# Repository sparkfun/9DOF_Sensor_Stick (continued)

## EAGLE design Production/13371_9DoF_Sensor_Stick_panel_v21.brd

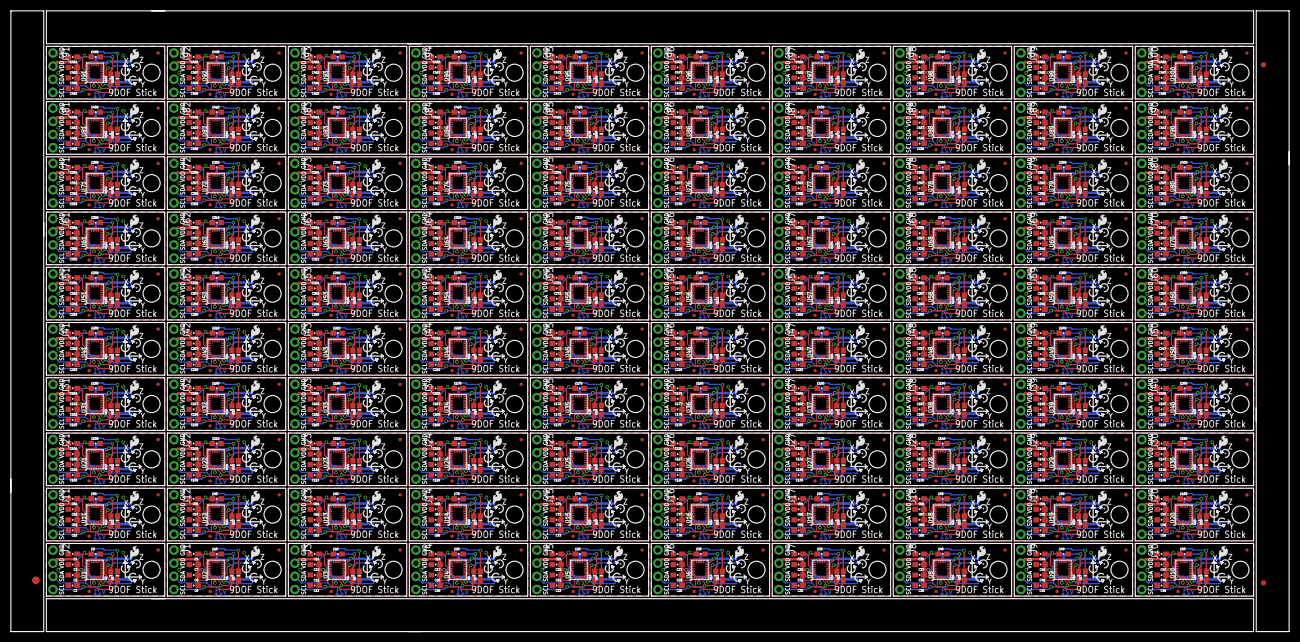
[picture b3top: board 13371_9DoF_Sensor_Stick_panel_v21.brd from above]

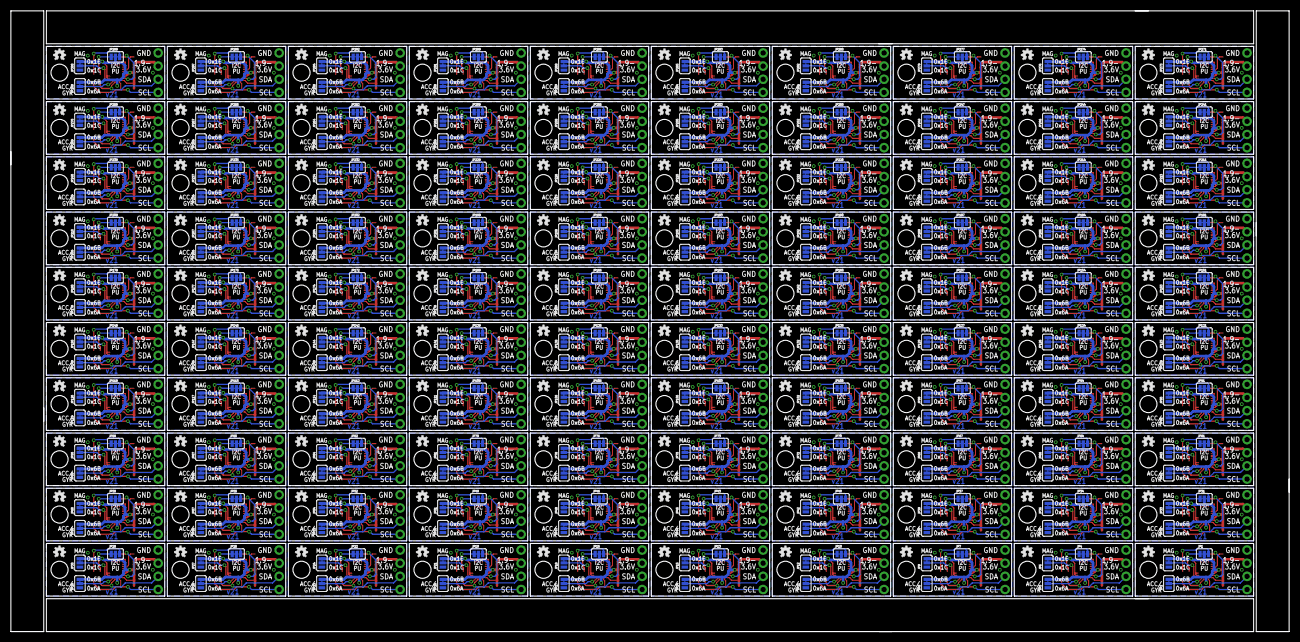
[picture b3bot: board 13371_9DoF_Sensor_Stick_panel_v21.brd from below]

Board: 2 copper layers, 246.9 x 119.9 mm, 1703 parts (400 on the bottom side), 1000 nets.

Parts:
C1, C6, C11, C16, C21, C26, C31, C36, C41, C46, C51, C56, C61, C66, C71, C76, C81, C86, C91, C96, C101, C106, C111, C116, C121, C126, C131, C136, C141, C146, C151, C156, C161, C166, C171, C176, C181, C186, C191, C196, C201, C206, C211, C216, C221, C226, C231, C236, C241, C246, C251, C256, C261, C266, C271, C276, C281, C286, C291, C296, C301, C306, C311, C316, C321, C326, C331, C336, C341, C346, C351, C356, C361, C366, C371, C376, C381, C386, C391, C396, C401, C406, C411, C416, C421, C426, C431, C436, C441, C446, C451, C456, C461, C466, C471, C476, C481, C486, C491, C496: 10uF; 0603-CAP
C2, C3, C5, C7, C8, C10, C12, C13, C15, C17, C18, C20, C22, C23, C25, C27, C28, C30, C32, C33, C35, C37, C38, C40, C42, C43, C45, C47, C48, C50, C52, C53, C55, C57, C58, C60, C62, C63, C65, C67, C68, C70, C72, C73, C75, C77, C78, C80, C82, C83, C85, C87, C88, C90, C92, C93, C95, C97, C98, C100, C102, C103, C105, C107, C108, C110, C112, C113, C115, C117, C118, C120, C122, C123, C125, C127, C128, C130, C132, C133, C135, C137, C138, C140, C142, C143, C145, C147, C148, C150, C152, C153, C155, C157, C158, C160, C162, C163, C165, C167, C168, C170, C172, C173, C175, C177, C178, C180, C182, C183, C185, C187, C188, C190, C192, C193, C195, C197, C198, C200, C202, C203, C205, C207, C208, C210, C212, C213, C215, C217, C218, C220, C222, C223, C225, C227, C228, C230, C232, C233, C235, C237, C238, C240, C242, C243, C245, C247, C248, C250, C252, C253, C255, C257, C258, C260, C262, C263, C265, C267, C268, C270, C272, C273, C275, C277, C278, C280, C282, C283, C285, C287, C288, C290, C292, C293, C295, C297, C298, C300, C302, C303, C305, C307, C308, C310, C312, C313, C315, C317, C318, C320, C322, C323, C325, C327, C328, C330, C332, C333, C335, C337, C338, C340, C342, C343, C345, C347, C348, C350, C352, C353, C355, C357, C358, C360, C362, C363, C365, C367, C368, C370, C372, C373, C375, C377, C378, C380, C382, C383, C385, C387, C388, C390, C392, C393, C395, C397, C398, C400, C402, C403, C405, C407, C408, C410, C412, C413, C415, C417, C418, C420, C422, C423, C425, C427, C428, C430, C432, C433, C435, C437, C438, C440, C442, C443, C445, C447, C448, C450, C452, C453, C455, C457, C458, C460, C462, C463, C465, C467, C468, C470, C472, C473, C475, C477, C478, C480, C482, C483, C485, C487, C488, C490, C492, C493, C495, C497, C498, C500: 0.1uF; 0603-CAP
C4, C9, C14, C19, C24, C29, C34, C39, C44, C49, C54, C59, C64, C69, C74, C79, C84, C89, C94, C99, C104, C109, C114, C119, C124, C129, C134, C139, C144, C149, C154, C159, C164, C169, C174, C179, C184, C189, C194, C199, C204, C209, C214, C219, C224, C229, C234, C239, C244, C249, C254, C259, C264, C269, C274, C279, C284, C289, C294, C299, C304, C309, C314, C319, C324, C329, C334, C339, C344, C349, C354, C359, C364, C369, C374, C379, C384, C389, C394, C399, C404, C409, C414, C419, C424, C429, C434, C439, C444, C449, C454, C459, C464, C469, C474, C479, C484, C489, C494, C499: 10nF; 0603-CAP
E$1: FIDUCIAL-1.5X3
E$7, E$8: FIDUCIAL-1X2
FD1, FD2, FD3, FD4, FD5, FD6, FD7, FD8, FD9, FD10, FD11, FD12, FD13, FD14, FD15, FD16, FD17, FD18, FD19, FD20, FD21, FD22, FD23, FD24, FD25, FD26, FD27, FD28, FD29, FD30, FD31, FD32, FD33, FD34, FD35, FD36, FD37, FD38, FD39, FD40, FD41, FD42, FD43, FD44, FD45, FD46, FD47, FD48, FD49, FD50, FD51, FD52, FD53, FD54, FD55, FD56, FD57, FD58, FD59, FD60, FD61, FD62, FD63, FD64, FD65, FD66, FD67, FD68, FD69, FD70, FD71, FD72, FD73, FD74, FD75, FD76, FD77, FD78, FD79, FD80, FD81, FD82, FD83, FD84, FD85, FD86, FD87, FD88, FD89, FD90, FD91, FD92, FD93, FD94, FD95, FD96, FD97, FD98, FD99, FD100, FD101, FD102, FD103, FD104, FD105, FD106, FD107, FD108, FD109, FD110, FD111, FD112, FD113, FD114, FD115, FD116, FD117, FD118, FD119, FD120, FD121, FD122, FD123, FD124, FD125, FD126, FD127, FD128, FD129, FD130, FD131, FD132, FD133, FD134, FD135, FD136, FD137, FD138, FD139, FD140, FD141, FD142, FD143, FD144, FD145, FD146, FD147, FD148, FD149, FD150, FD151, FD152, FD153, FD154, FD155, FD156, FD157, FD158, FD159, FD160, FD161, FD162, FD163, FD164, FD165, FD166, FD167, FD168, FD169, FD170, FD171, FD172, FD173, FD174, FD175, FD176, FD177, FD178, FD179, FD180, FD181, FD182, FD183, FD184, FD185, FD186, FD187, FD188, FD189, FD190, FD191, FD192, FD193, FD194, FD195, FD196, FD197, FD198, FD199, FD200: FIDUCIALUFIDUCIAL; MICRO-FIDUCIAL
H1, H2, H3, H4, H5, H6, H7, H8, H9, H10, H11, H12, H13, H14, H15, H16, H17, H18, H19, H20, H21, H22, H23, H24, H25, H26, H27, H28, H29, H30, H31, H32, H33, H34, H35, H36, H37, H38, H39, H40, H41, H42, H43, H44, H45, H46, H47, H48, H49, H50, H51, H52, H53, H54, H55, H56, H57, H58, H59, H60, H61, H62, H63, H64, H65, H66, H67, H68, H69, H70, H71, H72, H73, H74, H75, H76, H77, H78, H79, H80, H81, H82, H83, H84, H85, H86, H87, H88, H89, H90, H91, H92, H93, H94, H95, H96, H97, H98, H99, H100: STAND-OFF
J1, J2, J3, J4, J5, J6, J7, J8, J9, J10, J11, J12, J13, J14, J15, J16, J17, J18, J19, J20, J21, J22, J23, J24, J25, J26, J27, J28, J29, J30, J31, J32, J33, J34, J35, J36, J37, J38, J39, J40, J41, J42, J43, J44, J45, J46, J47, J48, J49, J50, J51, J52, J53, J54, J55, J56, J57, J58, J59, J60, J61, J62, J63, J64, J65, J66, J67, J68, J69, J70, J71, J72, J73, J74, J75, J76, J77, J78, J79, J80, J81, J82, J83, J84, J85, J86, J87, J88, J89, J90, J91, J92, J93, J94, J95, J96, J97, J98, J99, J100: 1X04_NO_SILK_ALL_ROUND
JP1, JP4, JP7, JP10, JP13, JP16, JP19, JP22, JP25, JP28, JP31, JP34, JP37, JP40, JP43, JP46, JP49, JP52, JP55, JP58, JP61, JP64, JP67, JP70, JP73, JP76, JP79, JP82, JP85, JP88, JP91, JP94, JP97, JP100, JP103, JP106, JP109, JP112, JP115, JP118, JP121, JP124, JP127, JP130, JP133, JP136, JP139, JP142, JP145, JP148, JP151, JP154, JP157, JP160, JP163, JP166, JP169, JP172, JP175, JP178, JP181, JP184, JP187, JP190, JP193, JP196, JP199, JP202, JP205, JP208, JP211, JP214, JP217, JP220, JP223, JP226, JP229, JP232, JP235, JP238, JP241, JP244, JP247, JP250, JP253, JP256, JP259, JP262, JP265, JP268, JP271, JP274, JP277, JP280, JP283, JP286, JP289, JP292, JP295, JP298: PAD-JUMPER-3-3OF3_NC_BY_TRACE_YES_SILK_FULL_BOX
JP2, JP3, JP5, JP6, JP8, JP9, JP11, JP12, JP14, JP15, JP17, JP18, JP20, JP21, JP23, JP24, JP26, JP27, JP29, JP30, JP32, JP33, JP35, JP36, JP38, JP39, JP41, JP42, JP44, JP45, JP47, JP48, JP50, JP51, JP53, JP54, JP56, JP57, JP59, JP60, JP62, JP63, JP65, JP66, JP68, JP69, JP71, JP72, JP74, JP75, JP77, JP78, JP80, JP81, JP83, JP84, JP86, JP87, JP89, JP90, JP92, JP93, JP95, JP96, JP98, JP99, JP101, JP102, JP104, JP105, JP107, JP108, JP110, JP111, JP113, JP114, JP116, JP117, JP119, JP120, JP122, JP123, JP125, JP126, JP128, JP129, JP131, JP132, JP134, JP135, JP137, JP138, JP140, JP141, JP143, JP144, JP146, JP147, JP149, JP150, JP152, JP153, JP155, JP156, JP158, JP159, JP161, JP162, JP164, JP165, JP167, JP168, JP170, JP171, JP173, JP174, JP176, JP177, JP179, JP180, JP182, JP183, JP185, JP186, JP188, JP189, JP191, JP192, JP194, JP195, JP197, JP198, JP200, JP201, JP203, JP204, JP206, JP207, JP209, JP210, JP212, JP213, JP215, JP216, JP218, JP219, JP221, JP222, JP224, JP225, JP227, JP228, JP230, JP231, JP233, JP234, JP236, JP237, JP239, JP240, JP242, JP243, JP245, JP246, JP248, JP249, JP251, JP252, JP254, JP255, JP257, JP258, JP260, JP261, JP263, JP264, JP266, JP267, JP269, JP270, JP272, JP273, JP275, JP276, JP278, JP279, JP281, JP282, JP284, JP285, JP287, JP288, JP290, JP291, JP293, JP294, JP296, JP297, JP299, JP300: PAD-JUMPER-3-2OF3_NC_BY_TRACE_YES_SILK_FULL_BOX
LOGO1, LOGO2, LOGO5, LOGO7, LOGO9, LOGO11, LOGO13, LOGO15, LOGO17, LOGO19, LOGO21, LOGO23, LOGO25, LOGO27, LOGO29, LOGO31, LOGO33, LOGO35, LOGO37, LOGO39, LOGO41, LOGO43, LOGO45, LOGO47, LOGO49, LOGO51, LOGO53, LOGO55, LOGO57, LOGO59, LOGO61, LOGO63, LOGO65, LOGO67, LOGO69, LOGO71, LOGO73, LOGO75, LOGO77, LOGO79, LOGO81, LOGO83, LOGO85, LOGO87, LOGO89, LOGO91, LOGO93, LOGO95, LOGO97, LOGO99, LOGO101, LOGO103, LOGO105, LOGO107, LOGO109, LOGO111, LOGO113, LOGO115, LOGO117, LOGO119, LOGO121, LOGO123, LOGO125, LOGO127, LOGO129, LOGO131, LOGO133, LOGO135, LOGO137, LOGO139, LOGO141, LOGO143, LOGO145, LOGO147, LOGO149, LOGO151, LOGO153, LOGO155, LOGO157, LOGO159, LOGO161, LOGO163, LOGO165, LOGO167, LOGO169, LOGO171, LOGO173, LOGO175, LOGO177, LOGO179, LOGO181, LOGO183, LOGO185, LOGO187, LOGO189, LOGO191, LOGO193, LOGO195, LOGO197, LOGO199: SFE_LOGO_FLAME.1_INCH; SFE_LOGO_FLAME_.1
LOGO3, LOGO4, LOGO6, LOGO8, LOGO10, LOGO12, LOGO14, LOGO16, LOGO18, LOGO20, LOGO22, LOGO24, LOGO26, LOGO28, LOGO30, LOGO32, LOGO34, LOGO36, LOGO38, LOGO40, LOGO42, LOGO44, LOGO46, LOGO48, LOGO50, LOGO52, LOGO54, LOGO56, LOGO58, LOGO60, LOGO62, LOGO64, LOGO66, LOGO68, LOGO70, LOGO72, LOGO74, LOGO76, LOGO78, LOGO80, LOGO82, LOGO84, LOGO86, LOGO88, LOGO90, LOGO92, LOGO94, LOGO96, LOGO98, LOGO100, LOGO102, LOGO104, LOGO106, LOGO108, LOGO110, LOGO112, LOGO114, LOGO116, LOGO118, LOGO120, LOGO122, LOGO124, LOGO126, LOGO128, LOGO130, LOGO132, LOGO134, LOGO136, LOGO138, LOGO140, LOGO142, LOGO144, LOGO146, LOGO148, LOGO150, LOGO152, LOGO154, LOGO156, LOGO158, LOGO160, LOGO162, LOGO164, LOGO166, LOGO168, LOGO170, LOGO172, LOGO174, LOGO176, LOGO178, LOGO180, LOGO182, LOGO184, LOGO186, LOGO188, LOGO190, LOGO192, LOGO194, LOGO196, LOGO198, LOGO200: OSHW-LOGOMINI; OSHW-LOGO-MINI
R1, R2, R3, R4, R5, R6, R7, R8, R9, R10, R11, R12, R13, R14, R15, R16, R17, R18, R19, R20, R21, R22, R23, R24, R25, R26, R27, R28, R29, R30, R31, R32, R33, R34, R35, R36, R37, R38, R39, R40, R41, R42, R43, R44, R45, R46, R47, R48, R49, R50, R51, R52, R53, R54, R55, R56, R57, R58, R59, R60, R61, R62, R63, R64, R65, R66, R67, R68, R69, R70, R71, R72, R73, R74, R75, R76, R77, R78, R79, R80, R81, R82, R83, R84, R85, R86, R87, R88, R89, R90, R91, R92, R93, R94, R95, R96, R97, R98, R99, R100, R101, R102, R103, R104, R105, R106, R107, R108, R109, R110, R111, R112, R113, R114, R115, R116, R117, R118, R119, R120, R121, R122, R123, R124, R125, R126, R127, R128, R129, R130, R131, R132, R133, R134, R135, R136, R137, R138, R139, R140, R141, R142, R143, R144, R145, R146, R147, R148, R149, R150, R151, R152, R153, R154, R155, R156, R157, R158, R159, R160, R161, R162, R163, R164, R165, R166, R167, R168, R169, R170, R171, R172, R173, R174, R175, R176, R177, R178, R179, R180, R181, R182, R183, R184, R185, R186, R187, R188, R189, R190, R191, R192, R193, R194, R195, R196, R197, R198, R199, R200: 4.7K; 0603-RES
U1, U2, U3, U4, U5, U6, U7, U8, U9, U10, U11, U12, U13, U14, U15, U16, U17, U18, U19, U20, U21, U22, U23, U24, U25, U26, U27, U28, U29, U30, U31, U32, U33, U34, U35, U36, U37, U38, U39, U40, U41, U42, U43, U44, U45, U46, U47, U48, U49, U50, U51, U52, U53, U54, U55, U56, U57, U58, U59, U60, U61, U62, U63, U64, U65, U66, U67, U68, U69, U70, U71, U72, U73, U74, U75, U76, U77, U78, U79, U80, U81, U82, U83, U84, U85, U86, U87, U88, U89, U90, U91, U92, U93, U94, U95, U96, U97, U98, U99, U100: LSM9DS1; LGA24-8X4

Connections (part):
GND: C1.2, C2.2, C3.2, C4.2, C5.2, J2.1, JP2.1, JP3.1, U1.14, U1.15, U1.16, U1.17, U1.18, U1.19, U1.20
GND1: C6.2, C7.2, C8.2, C9.2, C10.2, J1.1, JP5.1, JP6.1, U2.14, U2.15, U2.16, U2.17, U2.18, U2.19, U2.20
GND2: C11.2, C12.2, C13.2, C14.2, C15.2, J3.1, JP8.1, JP9.1, U3.14, U3.15, U3.16, U3.17, U3.18, U3.19, U3.20
GND3: C16.2, C17.2, C18.2, C19.2, C20.2, J4.1, JP11.1, JP12.1, U4.14, U4.15, U4.16, U4.17, U4.18, U4.19, U4.20
GND4: C21.2, C22.2, C23.2, C24.2, C25.2, J5.1, JP14.1, JP15.1, U5.14, U5.15, U5.16, U5.17, U5.18, U5.19, U5.20
GND5: C26.2, C27.2, C28.2, C29.2, C30.2, J6.1, JP17.1, JP18.1, U6.14, U6.15, U6.16, U6.17, U6.18, U6.19, U6.20
GND6: C31.2, C32.2, C33.2, C34.2, C35.2, J7.1, JP20.1, JP21.1, U7.14, U7.15, U7.16, U7.17, U7.18, U7.19, U7.20
GND7: C36.2, C37.2, C38.2, C39.2, C40.2, J8.1, JP23.1, JP24.1, U8.14, U8.15, U8.16, U8.17, U8.18, U8.19, U8.20
GND8: C41.2, C42.2, C43.2, C44.2, C45.2, J9.1, JP26.1, JP27.1, U9.14, U9.15, U9.16, U9.17, U9.18, U9.19, U9.20
GND9: C46.2, C47.2, C48.2, C49.2, C50.2, J10.1, JP29.1, JP30.1, U10.14, U10.15, U10.16, U10.17, U10.18, U10.19, U10.20
GND10: C51.2, C52.2, C53.2, C54.2, C55.2, J11.1, JP32.1, JP33.1, U11.14, U11.15, U11.16, U11.17, U11.18, U11.19, U11.20
GND11: C56.2, C57.2, C58.2, C59.2, C60.2, J12.1, JP35.1, JP36.1, U12.14, U12.15, U12.16, U12.17, U12.18, U12.19, U12.20
GND12: C61.2, C62.2, C63.2, C64.2, C65.2, J13.1, JP38.1, JP39.1, U13.14, U13.15, U13.16, U13.17, U13.18, U13.19, U13.20
GND13: C66.2, C67.2, C68.2, C69.2, C70.2, J14.1, JP41.1, JP42.1, U14.14, U14.15, U14.16, U14.17, U14.18, U14.19, U14.20
GND14: C71.2, C72.2, C73.2, C74.2, C75.2, J15.1, JP44.1, JP45.1, U15.14, U15.15, U15.16, U15.17, U15.18, U15.19, U15.20
GND15: C76.2, C77.2, C78.2, C79.2, C80.2, J16.1, JP47.1, JP48.1, U16.14, U16.15, U16.16, U16.17, U16.18, U16.19, U16.20
GND16: C81.2, C82.2, C83.2, C84.2, C85.2, J17.1, JP50.1, JP51.1, U17.14, U17.15, U17.16, U17.17, U17.18, U17.19, U17.20
GND17: C86.2, C87.2, C88.2, C89.2, C90.2, J18.1, JP53.1, JP54.1, U18.14, U18.15, U18.16, U18.17, U18.18, U18.19, U18.20
GND18: C91.2, C92.2, C93.2, C94.2, C95.2, J19.1, JP56.1, JP57.1, U19.14, U19.15, U19.16, U19.17, U19.18, U19.19, U19.20
GND19: C96.2, C97.2, C98.2, C99.2, C100.2, J20.1, JP59.1, JP60.1, U20.14, U20.15, U20.16, U20.17, U20.18, U20.19, U20.20
GND20: C101.2, C102.2, C103.2, C104.2, C105.2, J21.1, JP62.1, JP63.1, U21.14, U21.15, U21.16, U21.17, U21.18, U21.19, U21.20
GND21: C106.2, C107.2, C108.2, C109.2, C110.2, J22.1, JP65.1, JP66.1, U22.14, U22.15, U22.16, U22.17, U22.18, U22.19, U22.20
GND22: C111.2, C112.2, C113.2, C114.2, C115.2, J23.1, JP68.1, JP69.1, U23.14, U23.15, U23.16, U23.17, U23.18, U23.19, U23.20
GND23: C116.2, C117.2, C118.2, C119.2, C120.2, J24.1, JP71.1, JP72.1, U24.14, U24.15, U24.16, U24.17, U24.18, U24.19, U24.20
GND24: C121.2, C122.2, C123.2, C124.2, C125.2, J25.1, JP74.1, JP75.1, U25.14, U25.15, U25.16, U25.17, U25.18, U25.19, U25.20
GND25: C126.2, C127.2, C128.2, C129.2, C130.2, J26.1, JP77.1, JP78.1, U26.14, U26.15, U26.16, U26.17, U26.18, U26.19, U26.20
GND26: C131.2, C132.2, C133.2, C134.2, C135.2, J27.1, JP80.1, JP81.1, U27.14, U27.15, U27.16, U27.17, U27.18, U27.19, U27.20
GND27: C136.2, C137.2, C138.2, C139.2, C140.2, J28.1, JP83.1, JP84.1, U28.14, U28.15, U28.16, U28.17, U28.18, U28.19, U28.20
GND28: C141.2, C142.2, C143.2, C144.2, C145.2, J29.1, JP86.1, JP87.1, U29.14, U29.15, U29.16, U29.17, U29.18, U29.19, U29.20
GND29: C146.2, C147.2, C148.2, C149.2, C150.2, J30.1, JP89.1, JP90.1, U30.14, U30.15, U30.16, U30.17, U30.18, U30.19, U30.20
GND30: C151.2, C152.2, C153.2, C154.2, C155.2, J31.1, JP92.1, JP93.1, U31.14, U31.15, U31.16, U31.17, U31.18, U31.19, U31.20
GND31: C156.2, C157.2, C158.2, C159.2, C160.2, J32.1, JP95.1, JP96.1, U32.14, U32.15, U32.16, U32.17, U32.18, U32.19, U32.20
GND32: C161.2, C162.2, C163.2, C164.2, C165.2, J33.1, JP98.1, JP99.1, U33.14, U33.15, U33.16, U33.17, U33.18, U33.19, U33.20
GND33: C166.2, C167.2, C168.2, C169.2, C170.2, J34.1, JP101.1, JP102.1, U34.14, U34.15, U34.16, U34.17, U34.18, U34.19, U34.20
GND34: C171.2, C172.2, C173.2, C174.2, C175.2, J35.1, JP104.1, JP105.1, U35.14, U35.15, U35.16, U35.17, U35.18, U35.19, U35.20
GND35: C176.2, C177.2, C178.2, C179.2, C180.2, J36.1, JP107.1, JP108.1, U36.14, U36.15, U36.16, U36.17, U36.18, U36.19, U36.20
GND36: C181.2, C182.2, C183.2, C184.2, C185.2, J37.1, JP110.1, JP111.1, U37.14, U37.15, U37.16, U37.17, U37.18, U37.19, U37.20
GND37: C186.2, C187.2, C188.2, C189.2, C190.2, J38.1, JP113.1, JP114.1, U38.14, U38.15, U38.16, U38.17, U38.18, U38.19, U38.20
GND38: C191.2, C192.2, C193.2, C194.2, C195.2, J39.1, JP116.1, JP117.1, U39.14, U39.15, U39.16, U39.17, U39.18, U39.19, U39.20
GND39: C196.2, C197.2, C198.2, C199.2, C200.2, J40.1, JP119.1, JP120.1, U40.14, U40.15, U40.16, U40.17, U40.18, U40.19, U40.20
GND40: C201.2, C202.2, C203.2, C204.2, C205.2, J41.1, JP122.1, JP123.1, U41.14, U41.15, U41.16, U41.17, U41.18, U41.19, U41.20
GND41: C206.2, C207.2, C208.2, C209.2, C210.2, J42.1, JP125.1, JP126.1, U42.14, U42.15, U42.16, U42.17, U42.18, U42.19, U42.20
GND42: C211.2, C212.2, C213.2, C214.2, C215.2, J43.1, JP128.1, JP129.1, U43.14, U43.15, U43.16, U43.17, U43.18, U43.19, U43.20
GND43: C216.2, C217.2, C218.2, C219.2, C220.2, J44.1, JP131.1, JP132.1, U44.14, U44.15, U44.16, U44.17, U44.18, U44.19, U44.20
GND44: C221.2, C222.2, C223.2, C224.2, C225.2, J45.1, JP134.1, JP135.1, U45.14, U45.15, U45.16, U45.17, U45.18, U45.19, U45.20
GND45: C226.2, C227.2, C228.2, C229.2, C230.2, J46.1, JP137.1, JP138.1, U46.14, U46.15, U46.16, U46.17, U46.18, U46.19, U46.20
GND46: C231.2, C232.2, C233.2, C234.2, C235.2, J47.1, JP140.1, JP141.1, U47.14, U47.15, U47.16, U47.17, U47.18, U47.19, U47.20
GND47: C236.2, C237.2, C238.2, C239.2, C240.2, J48.1, JP143.1, JP144.1, U48.14, U48.15, U48.16, U48.17, U48.18, U48.19, U48.20
GND48: C241.2, C242.2, C243.2, C244.2, C245.2, J49.1, JP146.1, JP147.1, U49.14, U49.15, U49.16, U49.17, U49.18, U49.19, U49.20
GND49: C246.2, C247.2, C248.2, C249.2, C250.2, J50.1, JP149.1, JP150.1, U50.14, U50.15, U50.16, U50.17, U50.18, U50.19, U50.20
GND50: C251.2, C252.2, C253.2, C254.2, C255.2, J51.1, JP152.1, JP153.1, U51.14, U51.15, U51.16, U51.17, U51.18, U51.19, U51.20
GND51: C256.2, C257.2, C258.2, C259.2, C260.2, J52.1, JP155.1, JP156.1, U52.14, U52.15, U52.16, U52.17, U52.18, U52.19, U52.20
GND52: C261.2, C262.2, C263.2, C264.2, C265.2, J53.1, JP158.1, JP159.1, U53.14, U53.15, U53.16, U53.17, U53.18, U53.19, U53.20
GND53: C266.2, C267.2, C268.2, C269.2, C270.2, J54.1, JP161.1, JP162.1, U54.14, U54.15, U54.16, U54.17, U54.18, U54.19, U54.20
GND54: C271.2, C272.2, C273.2, C274.2, C275.2, J55.1, JP164.1, JP165.1, U55.14, U55.15, U55.16, U55.17, U55.18, U55.19, U55.20
GND55: C276.2, C277.2, C278.2, C279.2, C280.2, J56.1, JP167.1, JP168.1, U56.14, U56.15, U56.16, U56.17, U56.18, U56.19, U56.20
GND56: C281.2, C282.2, C283.2, C284.2, C285.2, J57.1, JP170.1, JP171.1, U57.14, U57.15, U57.16, U57.17, U57.18, U57.19, U57.20
GND57: C286.2, C287.2, C288.2, C289.2, C290.2, J58.1, JP173.1, JP174.1, U58.14, U58.15, U58.16, U58.17, U58.18, U58.19, U58.20
GND58: C291.2, C292.2, C293.2, C294.2, C295.2, J59.1, JP176.1, JP177.1, U59.14, U59.15, U59.16, U59.17, U59.18, U59.19, U59.20
GND59: C296.2, C297.2, C298.2, C299.2, C300.2, J60.1, JP179.1, JP180.1, U60.14, U60.15, U60.16, U60.17, U60.18, U60.19, U60.20
GND60: C301.2, C302.2, C303.2, C304.2, C305.2, J61.1, JP182.1, JP183.1, U61.14, U61.15, U61.16, U61.17, U61.18, U61.19, U61.20
GND61: C306.2, C307.2, C308.2, C309.2, C310.2, J62.1, JP185.1, JP186.1, U62.14, U62.15, U62.16, U62.17, U62.18, U62.19, U62.20
GND62: C311.2, C312.2, C313.2, C314.2, C315.2, J63.1, JP188.1, JP189.1, U63.14, U63.15, U63.16, U63.17, U63.18, U63.19, U63.20
GND63: C316.2, C317.2, C318.2, C319.2, C320.2, J64.1, JP191.1, JP192.1, U64.14, U64.15, U64.16, U64.17, U64.18, U64.19, U64.20
GND64: C321.2, C322.2, C323.2, C324.2, C325.2, J65.1, JP194.1, JP195.1, U65.14, U65.15, U65.16, U65.17, U65.18, U65.19, U65.20
GND65: C326.2, C327.2, C328.2, C329.2, C330.2, J66.1, JP197.1, JP198.1, U66.14, U66.15, U66.16, U66.17, U66.18, U66.19, U66.20
GND66: C331.2, C332.2, C333.2, C334.2, C335.2, J67.1, JP200.1, JP201.1, U67.14, U67.15, U67.16, U67.17, U67.18, U67.19, U67.20
GND67: C336.2, C337.2, C338.2, C339.2, C340.2, J68.1, JP203.1, JP204.1, U68.14, U68.15, U68.16, U68.17, U68.18, U68.19, U68.20
GND68: C341.2, C342.2, C343.2, C344.2, C345.2, J69.1, JP206.1, JP207.1, U69.14, U69.15, U69.16, U69.17, U69.18, U69.19, U69.20
GND69: C346.2, C347.2, C348.2, C349.2, C350.2, J70.1, JP209.1, JP210.1, U70.14, U70.15, U70.16, U70.17, U70.18, U70.19, U70.20
GND70: C351.2, C352.2, C353.2, C354.2, C355.2, J71.1, JP212.1, JP213.1, U71.14, U71.15, U71.16, U71.17, U71.18, U71.19, U71.20
GND71: C356.2, C357.2, C358.2, C359.2, C360.2, J72.1, JP215.1, JP216.1, U72.14, U72.15, U72.16, U72.17, U72.18, U72.19, U72.20
GND72: C361.2, C362.2, C363.2, C364.2, C365.2, J73.1, JP218.1, JP219.1, U73.14, U73.15, U73.16, U73.17, U73.18, U73.19, U73.20
GND73: C366.2, C367.2, C368.2, C369.2, C370.2, J74.1, JP221.1, JP222.1, U74.14, U74.15, U74.16, U74.17, U74.18, U74.19, U74.20
GND74: C371.2, C372.2, C373.2, C374.2, C375.2, J75.1, JP224.1, JP225.1, U75.14, U75.15, U75.16, U75.17, U75.18, U75.19, U75.20
GND75: C376.2, C377.2, C378.2, C379.2, C380.2, J76.1, JP227.1, JP228.1, U76.14, U76.15, U76.16, U76.17, U76.18, U76.19, U76.20
GND76: C381.2, C382.2, C383.2, C384.2, C385.2, J77.1, JP230.1, JP231.1, U77.14, U77.15, U77.16, U77.17, U77.18, U77.19, U77.20
GND77: C386.2, C387.2, C388.2, C389.2, C390.2, J78.1, JP233.1, JP234.1, U78.14, U78.15, U78.16, U78.17, U78.18, U78.19, U78.20
GND78: C391.2, C392.2, C393.2, C394.2, C395.2, J79.1, JP236.1, JP237.1, U79.14, U79.15, U79.16, U79.17, U79.18, U79.19, U79.20
GND79: C396.2, C397.2, C398.2, C399.2, C400.2, J80.1, JP239.1, JP240.1, U80.14, U80.15, U80.16, U80.17, U80.18, U80.19, U80.20
GND80: C401.2, C402.2, C403.2, C404.2, C405.2, J81.1, JP242.1, JP243.1, U81.14, U81.15, U81.16, U81.17, U81.18, U81.19, U81.20
GND81: C406.2, C407.2, C408.2, C409.2, C410.2, J82.1, JP245.1, JP246.1, U82.14, U82.15, U82.16, U82.17, U82.18, U82.19, U82.20
GND82: C411.2, C412.2, C413.2, C414.2, C415.2, J83.1, JP248.1, JP249.1, U83.14, U83.15, U83.16, U83.17, U83.18, U83.19, U83.20
GND83: C416.2, C417.2, C418.2, C419.2, C420.2, J84.1, JP251.1, JP252.1, U84.14, U84.15, U84.16, U84.17, U84.18, U84.19, U84.20
GND84: C421.2, C422.2, C423.2, C424.2, C425.2, J85.1, JP254.1, JP255.1, U85.14, U85.15, U85.16, U85.17, U85.18, U85.19, U85.20
GND85: C426.2, C427.2, C428.2, C429.2, C430.2, J86.1, JP257.1, JP258.1, U86.14, U86.15, U86.16, U86.17, U86.18, U86.19, U86.20
GND86: C431.2, C432.2, C433.2, C434.2, C435.2, J87.1, JP260.1, JP261.1, U87.14, U87.15, U87.16, U87.17, U87.18, U87.19, U87.20
GND87: C436.2, C437.2, C438.2, C439.2, C440.2, J88.1, JP263.1, JP264.1, U88.14, U88.15, U88.16, U88.17, U88.18, U88.19, U88.20
GND88: C441.2, C442.2, C443.2, C444.2, C445.2, J89.1, JP266.1, JP267.1, U89.14, U89.15, U89.16, U89.17, U89.18, U89.19, U89.20
GND89: C446.2, C447.2, C448.2, C449.2, C450.2, J90.1, JP269.1, JP270.1, U90.14, U90.15, U90.16, U90.17, U90.18, U90.19, U90.20
GND90: C451.2, C452.2, C453.2, C454.2, C455.2, J91.1, JP272.1, JP273.1, U91.14, U91.15, U91.16, U91.17, U91.18, U91.19, U91.20
GND91: C456.2, C457.2, C458.2, C459.2, C460.2, J92.1, JP275.1, JP276.1, U92.14, U92.15, U92.16, U92.17, U92.18, U92.19, U92.20
GND92: C461.2, C462.2, C463.2, C464.2, C465.2, J93.1, JP278.1, JP279.1, U93.14, U93.15, U93.16, U93.17, U93.18, U93.19, U93.20
GND93: C466.2, C467.2, C468.2, C469.2, C470.2, J94.1, JP281.1, JP282.1, U94.14, U94.15, U94.16, U94.17, U94.18, U94.19, U94.20
GND94: C471.2, C472.2, C473.2, C474.2, C475.2, J95.1, JP284.1, JP285.1, U95.14, U95.15, U95.16, U95.17, U95.18, U95.19, U95.20
GND95: C476.2, C477.2, C478.2, C479.2, C480.2, J96.1, JP287.1, JP288.1, U96.14, U96.15, U96.16, U96.17, U96.18, U96.19, U96.20
GND96: C481.2, C482.2, C483.2, C484.2, C485.2, J97.1, JP290.1, JP291.1, U97.14, U97.15, U97.16, U97.17, U97.18, U97.19, U97.20
GND97: C486.2, C487.2, C488.2, C489.2, C490.2, J98.1, JP293.1, JP294.1, U98.14, U98.15, U98.16, U98.17, U98.18, U98.19, U98.20
GND98: C491.2, C492.2, C493.2, C494.2, C495.2, J99.1, JP296.1, JP297.1, U99.14, U99.15, U99.16, U99.17, U99.18, U99.19, U99.20
GND99: C496.2, C497.2, C498.2, C499.2, C500.2, J100.1, JP299.1, JP300.1, U100.14, U100.15, U100.16, U100.17, U100.18, U100.19, U100.20
unnamed: JP1.1, R2.2
unnamed: JP1.3, R1.2
unnamed: JP4.1, R4.2
unnamed: JP4.3, R3.2
unnamed: C4.1, U1.21
unnamed: C5.1, U1.24
unnamed: C9.1, U2.21
unnamed: C10.1, U2.24
unnamed: JP7.1, R6.2
unnamed: JP7.3, R5.2
unnamed: C14.1, U3.21
unnamed: C15.1, U3.24
unnamed: JP10.1, R8.2
unnamed: JP10.3, R7.2
unnamed: C19.1, U4.21
unnamed: C20.1, U4.24
unnamed: JP13.1, R10.2
unnamed: JP13.3, R9.2
unnamed: C24.1, U5.21
unnamed: C25.1, U5.24
unnamed: JP16.1, R12.2
unnamed: JP16.3, R11.2
unnamed: C29.1, U6.21
unnamed: C30.1, U6.24
unnamed: JP19.1, R14.2
unnamed: JP19.3, R13.2
unnamed: C34.1, U7.21
unnamed: C35.1, U7.24
unnamed: JP22.1, R16.2
unnamed: JP22.3, R15.2
unnamed: C39.1, U8.21
unnamed: C40.1, U8.24
unnamed: JP25.1, R18.2
unnamed: JP25.3, R17.2
unnamed: C44.1, U9.21
unnamed: C45.1, U9.24
unnamed: JP28.1, R20.2
unnamed: JP28.3, R19.2
unnamed: C49.1, U10.21
unnamed: C50.1, U10.24
unnamed: JP31.1, R22.2
unnamed: JP31.3, R21.2
unnamed: C54.1, U11.21
unnamed: C55.1, U11.24
unnamed: JP34.1, R24.2
unnamed: JP34.3, R23.2
unnamed: C59.1, U12.21
unnamed: C60.1, U12.24
unnamed: JP37.1, R26.2
unnamed: JP37.3, R25.2
unnamed: C64.1, U13.21
unnamed: C65.1, U13.24
unnamed: JP40.1, R28.2
unnamed: JP40.3, R27.2
unnamed: C69.1, U14.21
unnamed: C70.1, U14.24
unnamed: JP43.1, R30.2
unnamed: JP43.3, R29.2
unnamed: C74.1, U15.21
unnamed: C75.1, U15.24
unnamed: JP46.1, R32.2
unnamed: JP46.3, R31.2
unnamed: C79.1, U16.21
unnamed: C80.1, U16.24
unnamed: JP49.1, R34.2
unnamed: JP49.3, R33.2
unnamed: C84.1, U17.21
unnamed: C85.1, U17.24
unnamed: JP52.1, R36.2
unnamed: JP52.3, R35.2
unnamed: C89.1, U18.21
unnamed: C90.1, U18.24
unnamed: JP55.1, R38.2
unnamed: JP55.3, R37.2
unnamed: C94.1, U19.21
unnamed: C95.1, U19.24
unnamed: JP58.1, R40.2
unnamed: JP58.3, R39.2
unnamed: C99.1, U20.21
unnamed: C100.1, U20.24
unnamed: JP61.1, R42.2
unnamed: JP61.3, R41.2
unnamed: C104.1, U21.21
unnamed: C105.1, U21.24
unnamed: JP64.1, R44.2
unnamed: JP64.3, R43.2
unnamed: C109.1, U22.21
unnamed: C110.1, U22.24
unnamed: JP67.1, R46.2
unnamed: JP67.3, R45.2
unnamed: C114.1, U23.21
unnamed: C115.1, U23.24
unnamed: JP70.1, R48.2
unnamed: JP70.3, R47.2
unnamed: C119.1, U24.21
unnamed: C120.1, U24.24
unnamed: JP73.1, R50.2
unnamed: JP73.3, R49.2
unnamed: C124.1, U25.21
unnamed: C125.1, U25.24
unnamed: JP76.1, R52.2
unnamed: JP76.3, R51.2
unnamed: C129.1, U26.21
unnamed: C130.1, U26.24
unnamed: JP79.1, R54.2
unnamed: JP79.3, R53.2
unnamed: C134.1, U27.21
unnamed: C135.1, U27.24
unnamed: JP82.1, R56.2
unnamed: JP82.3, R55.2
unnamed: C139.1, U28.21
unnamed: C140.1, U28.24
unnamed: JP85.1, R58.2
unnamed: JP85.3, R57.2
unnamed: C144.1, U29.21
unnamed: C145.1, U29.24
unnamed: JP88.1, R60.2
unnamed: JP88.3, R59.2
unnamed: C149.1, U30.21
unnamed: C150.1, U30.24
unnamed: JP91.1, R62.2
unnamed: JP91.3, R61.2
unnamed: C154.1, U31.21
unnamed: C155.1, U31.24
unnamed: JP94.1, R64.2
unnamed: JP94.3, R63.2
unnamed: C159.1, U32.21
unnamed: C160.1, U32.24
unnamed: JP97.1, R66.2
unnamed: JP97.3, R65.2
unnamed: C164.1, U33.21
unnamed: C165.1, U33.24
unnamed: JP100.1, R68.2
unnamed: JP100.3, R67.2
unnamed: C169.1, U34.21
unnamed: C170.1, U34.24
unnamed: JP103.1, R70.2
unnamed: JP103.3, R69.2
unnamed: C174.1, U35.21
unnamed: C175.1, U35.24
unnamed: JP106.1, R72.2
unnamed: JP106.3, R71.2
unnamed: C179.1, U36.21
unnamed: C180.1, U36.24
unnamed: JP109.1, R74.2
unnamed: JP109.3, R73.2
unnamed: C184.1, U37.21
unnamed: C185.1, U37.24
unnamed: JP112.1, R76.2
unnamed: JP112.3, R75.2
unnamed: C189.1, U38.21
unnamed: C190.1, U38.24
unnamed: JP115.1, R78.2
unnamed: JP115.3, R77.2
unnamed: C194.1, U39.21
unnamed: C195.1, U39.24
unnamed: JP118.1, R80.2
unnamed: JP118.3, R79.2
unnamed: C199.1, U40.21
unnamed: C200.1, U40.24
unnamed: JP121.1, R82.2
unnamed: JP121.3, R81.2
unnamed: C204.1, U41.21
unnamed: C205.1, U41.24
unnamed: JP124.1, R84.2
unnamed: JP124.3, R83.2
unnamed: C209.1, U42.21
unnamed: C210.1, U42.24
unnamed: JP127.1, R86.2
unnamed: JP127.3, R85.2
unnamed: C214.1, U43.21
unnamed: C215.1, U43.24
unnamed: JP130.1, R88.2
unnamed: JP130.3, R87.2
unnamed: C219.1, U44.21
unnamed: C220.1, U44.24
unnamed: JP133.1, R90.2
unnamed: JP133.3, R89.2
unnamed: C224.1, U45.21
unnamed: C225.1, U45.24
unnamed: JP136.1, R92.2
unnamed: JP136.3, R91.2
unnamed: C229.1, U46.21
unnamed: C230.1, U46.24
unnamed: JP139.1, R94.2
unnamed: JP139.3, R93.2
unnamed: C234.1, U47.21
unnamed: C235.1, U47.24
unnamed: JP142.1, R96.2
unnamed: JP142.3, R95.2
unnamed: C239.1, U48.21
unnamed: C240.1, U48.24
unnamed: JP145.1, R98.2
unnamed: JP145.3, R97.2
unnamed: C244.1, U49.21
unnamed: C245.1, U49.24
unnamed: JP148.1, R100.2
unnamed: JP148.3, R99.2
unnamed: C249.1, U50.21
unnamed: C250.1, U50.24
unnamed: JP151.1, R102.2
unnamed: JP151.3, R101.2
unnamed: C254.1, U51.21
unnamed: C255.1, U51.24
unnamed: JP154.1, R104.2
unnamed: JP154.3, R103.2
unnamed: C259.1, U52.21
unnamed: C260.1, U52.24
unnamed: JP157.1, R106.2
unnamed: JP157.3, R105.2
unnamed: C264.1, U53.21
unnamed: C265.1, U53.24
unnamed: JP160.1, R108.2
unnamed: JP160.3, R107.2
unnamed: C269.1, U54.21
unnamed: C270.1, U54.24
unnamed: JP163.1, R110.2
unnamed: JP163.3, R109.2
unnamed: C274.1, U55.21
unnamed: C275.1, U55.24
unnamed: JP166.1, R112.2
unnamed: JP166.3, R111.2
unnamed: C279.1, U56.21
unnamed: C280.1, U56.24
unnamed: JP169.1, R114.2
unnamed: JP169.3, R113.2
unnamed: C284.1, U57.21
unnamed: C285.1, U57.24
unnamed: JP172.1, R116.2
unnamed: JP172.3, R115.2
unnamed: C289.1, U58.21
unnamed: C290.1, U58.24
unnamed: JP175.1, R118.2
unnamed: JP175.3, R117.2
unnamed: C294.1, U59.21
unnamed: C295.1, U59.24
unnamed: JP178.1, R120.2
unnamed: JP178.3, R119.2
unnamed: C299.1, U60.21
unnamed: C300.1, U60.24
unnamed: JP181.1, R122.2
unnamed: JP181.3, R121.2
unnamed: C304.1, U61.21
unnamed: C305.1, U61.24
unnamed: JP184.1, R124.2
unnamed: JP184.3, R123.2
unnamed: C309.1, U62.21
unnamed: C310.1, U62.24
unnamed: JP187.1, R126.2
unnamed: JP187.3, R125.2
unnamed: C314.1, U63.21
unnamed: C315.1, U63.24
unnamed: JP190.1, R128.2
unnamed: JP190.3, R127.2
unnamed: C319.1, U64.21
unnamed: C320.1, U64.24
unnamed: JP193.1, R130.2
unnamed: JP193.3, R129.2
unnamed: C324.1, U65.21
unnamed: C325.1, U65.24
unnamed: JP196.1, R132.2
unnamed: JP196.3, R131.2
unnamed: C329.1, U66.21
unnamed: C330.1, U66.24
unnamed: JP199.1, R134.2
unnamed: JP199.3, R133.2
unnamed: C334.1, U67.21
unnamed: C335.1, U67.24
unnamed: JP202.1, R136.2
unnamed: JP202.3, R135.2
unnamed: C339.1, U68.21
unnamed: C340.1, U68.24
unnamed: JP205.1, R138.2
unnamed: JP205.3, R137.2
unnamed: C344.1, U69.21
unnamed: C345.1, U69.24
unnamed: JP208.1, R140.2
unnamed: JP208.3, R139.2
unnamed: C349.1, U70.21
unnamed: C350.1, U70.24
unnamed: JP211.1, R142.2
unnamed: JP211.3, R141.2
unnamed: C354.1, U71.21
unnamed: C355.1, U71.24
unnamed: JP214.1, R144.2
unnamed: JP214.3, R143.2
unnamed: C359.1, U72.21
unnamed: C360.1, U72.24
unnamed: JP217.1, R146.2
unnamed: JP217.3, R145.2
unnamed: C364.1, U73.21
unnamed: C365.1, U73.24
unnamed: JP220.1, R148.2
unnamed: JP220.3, R147.2
unnamed: C369.1, U74.21
unnamed: C370.1, U74.24
unnamed: JP223.1, R150.2
unnamed: JP223.3, R149.2
unnamed: C374.1, U75.21
unnamed: C375.1, U75.24
unnamed: JP226.1, R152.2
unnamed: JP226.3, R151.2
unnamed: C379.1, U76.21
unnamed: C380.1, U76.24
unnamed: JP229.1, R154.2
unnamed: JP229.3, R153.2
unnamed: C384.1, U77.21
unnamed: C385.1, U77.24
unnamed: JP232.1, R156.2
unnamed: JP232.3, R155.2
unnamed: C389.1, U78.21
unnamed: C390.1, U78.24
unnamed: JP235.1, R158.2
unnamed: JP235.3, R157.2
unnamed: C394.1, U79.21
unnamed: C395.1, U79.24
unnamed: JP238.1, R160.2
unnamed: JP238.3, R159.2
unnamed: C399.1, U80.21
unnamed: C400.1, U80.24
unnamed: JP241.1, R162.2
unnamed: JP241.3, R161.2
unnamed: C404.1, U81.21
unnamed: C405.1, U81.24
unnamed: JP244.1, R164.2
unnamed: JP244.3, R163.2
unnamed: C409.1, U82.21
unnamed: C410.1, U82.24
unnamed: JP247.1, R166.2
unnamed: JP247.3, R165.2
unnamed: C414.1, U83.21
unnamed: C415.1, U83.24
unnamed: JP250.1, R168.2
unnamed: JP250.3, R167.2
unnamed: C419.1, U84.21
unnamed: C420.1, U84.24
unnamed: JP253.1, R170.2
unnamed: JP253.3, R169.2
unnamed: C424.1, U85.21
unnamed: C425.1, U85.24
unnamed: JP256.1, R172.2
unnamed: JP256.3, R171.2
unnamed: C429.1, U86.21
unnamed: C430.1, U86.24
unnamed: JP259.1, R174.2
unnamed: JP259.3, R173.2
unnamed: C434.1, U87.21
unnamed: C435.1, U87.24
unnamed: JP262.1, R176.2
unnamed: JP262.3, R175.2
unnamed: C439.1, U88.21
unnamed: C440.1, U88.24
unnamed: JP265.1, R178.2
unnamed: JP265.3, R177.2
unnamed: C444.1, U89.21
unnamed: C445.1, U89.24
unnamed: JP268.1, R180.2
unnamed: JP268.3, R179.2
unnamed: C449.1, U90.21
unnamed: C450.1, U90.24
unnamed: JP271.1, R182.2
unnamed: JP271.3, R181.2
unnamed: C454.1, U91.21
unnamed: C455.1, U91.24
unnamed: JP274.1, R184.2
unnamed: JP274.3, R183.2
unnamed: C459.1, U92.21
unnamed: C460.1, U92.24
unnamed: JP277.1, R186.2
unnamed: JP277.3, R185.2
unnamed: C464.1, U93.21
unnamed: C465.1, U93.24
unnamed: JP280.1, R188.2
unnamed: JP280.3, R187.2
unnamed: C469.1, U94.21
unnamed: C470.1, U94.24
unnamed: JP283.1, R190.2
unnamed: JP283.3, R189.2
unnamed: C474.1, U95.21
unnamed: C475.1, U95.24
unnamed: JP286.1, R192.2
unnamed: JP286.3, R191.2
unnamed: C479.1, U96.21
unnamed: C480.1, U96.24
unnamed: JP289.1, R194.2
unnamed: JP289.3, R193.2
unnamed: C484.1, U97.21
unnamed: C485.1, U97.24
unnamed: JP292.1, R196.2
unnamed: JP292.3, R195.2
unnamed: C489.1, U98.21
unnamed: C490.1, U98.24
unnamed: JP295.1, R198.2
unnamed: JP295.3, R197.2
unnamed: C494.1, U99.21
unnamed: C495.1, U99.24
unnamed: JP298.1, R200.2
unnamed: JP298.3, R199.2
unnamed: C499.1, U100.21
unnamed: C500.1, U100.24
SCL: J2.4, R1.1, U1.2
SCL1: J1.4, R3.1, U2.2
SCL2: J3.4, R5.1, U3.2
SCL3: J4.4, R7.1, U4.2
SCL4: J5.4, R9.1, U5.2
SCL5: J6.4, R11.1, U6.2
SCL6: J7.4, R13.1, U7.2
SCL7: J8.4, R15.1, U8.2
SCL8: J9.4, R17.1, U9.2
SCL9: J10.4, R19.1, U10.2
SCL10: J11.4, R21.1, U11.2
SCL11: J12.4, R23.1, U12.2
SCL12: J13.4, R25.1, U13.2
SCL13: J14.4, R27.1, U14.2
SCL14: J15.4, R29.1, U15.2
SCL15: J16.4, R31.1, U16.2
SCL16: J17.4, R33.1, U17.2
SCL17: J18.4, R35.1, U18.2
SCL18: J19.4, R37.1, U19.2
SCL19: J20.4, R39.1, U20.2
SCL20: J21.4, R41.1, U21.2
SCL21: J22.4, R43.1, U22.2
SCL22: J23.4, R45.1, U23.2
SCL23: J24.4, R47.1, U24.2
SCL24: J25.4, R49.1, U25.2
SCL25: J26.4, R51.1, U26.2
SCL26: J27.4, R53.1, U27.2
SCL27: J28.4, R55.1, U28.2
SCL28: J29.4, R57.1, U29.2
SCL29: J30.4, R59.1, U30.2
SCL30: J31.4, R61.1, U31.2
SCL31: J32.4, R63.1, U32.2
SCL32: J33.4, R65.1, U33.2
SCL33: J34.4, R67.1, U34.2
SCL34: J35.4, R69.1, U35.2
SCL35: J36.4, R71.1, U36.2
SCL36: J37.4, R73.1, U37.2
SCL37: J38.4, R75.1, U38.2
SCL38: J39.4, R77.1, U39.2
SCL39: J40.4, R79.1, U40.2
SCL40: J41.4, R81.1, U41.2
SCL41: J42.4, R83.1, U42.2
SCL42: J43.4, R85.1, U43.2
SCL43: J44.4, R87.1, U44.2
SCL44: J45.4, R89.1, U45.2
SCL45: J46.4, R91.1, U46.2
SCL46: J47.4, R93.1, U47.2
SCL47: J48.4, R95.1, U48.2
SCL48: J49.4, R97.1, U49.2
SCL49: J50.4, R99.1, U50.2
SCL50: J51.4, R101.1, U51.2
SCL51: J52.4, R103.1, U52.2
SCL52: J53.4, R105.1, U53.2
SCL53: J54.4, R107.1, U54.2
SCL54: J55.4, R109.1, U55.2
SCL55: J56.4, R111.1, U56.2
SCL56: J57.4, R113.1, U57.2
SCL57: J58.4, R115.1, U58.2
SCL58: J59.4, R117.1, U59.2
SCL59: J60.4, R119.1, U60.2
SCL60: J61.4, R121.1, U61.2
SCL61: J62.4, R123.1, U62.2
SCL62: J63.4, R125.1, U63.2
SCL63: J64.4, R127.1, U64.2
SCL64: J65.4, R129.1, U65.2
SCL65: J66.4, R131.1, U66.2
SCL66: J67.4, R133.1, U67.2
SCL67: J68.4, R135.1, U68.2
SCL68: J69.4, R137.1, U69.2
SCL69: J70.4, R139.1, U70.2
SCL70: J71.4, R141.1, U71.2
SCL71: J72.4, R143.1, U72.2
SCL72: J73.4, R145.1, U73.2
SCL73: J74.4, R147.1, U74.2
SCL74: J75.4, R149.1, U75.2
SCL75: J76.4, R151.1, U76.2
SCL76: J77.4, R153.1, U77.2
SCL77: J78.4, R155.1, U78.2
SCL78: J79.4, R157.1, U79.2
SCL79: J80.4, R159.1, U80.2
SCL80: J81.4, R161.1, U81.2
SCL81: J82.4, R163.1, U82.2
SCL82: J83.4, R165.1, U83.2
SCL83: J84.4, R167.1, U84.2
SCL84: J85.4, R169.1, U85.2
SCL85: J86.4, R171.1, U86.2
SCL86: J87.4, R173.1, U87.2
SCL87: J88.4, R175.1, U88.2
SCL88: J89.4, R177.1, U89.2
SCL89: J90.4, R179.1, U90.2
SCL90: J91.4, R181.1, U91.2
SCL91: J92.4, R183.1, U92.2
SCL92: J93.4, R185.1, U93.2
SCL93: J94.4, R187.1, U94.2
SCL94: J95.4, R189.1, U95.2
SCL95: J96.4, R191.1, U96.2
SCL96: J97.4, R193.1, U97.2
SCL97: J98.4, R195.1, U98.2
SCL98: J99.4, R197.1, U99.2
SCL99: J100.4, R199.1, U100.2
SDA: J2.3, R2.1, U1.4
SDA1: J1.3, R4.1, U2.4
SDA2: J3.3, R6.1, U3.4
SDA3: J4.3, R8.1, U4.4
SDA4: J5.3, R10.1, U5.4
SDA5: J6.3, R12.1, U6.4
SDA6: J7.3, R14.1, U7.4
SDA7: J8.3, R16.1, U8.4
SDA8: J9.3, R18.1, U9.4
SDA9: J10.3, R20.1, U10.4
SDA10: J11.3, R22.1, U11.4
SDA11: J12.3, R24.1, U12.4
SDA12: J13.3, R26.1, U13.4
SDA13: J14.3, R28.1, U14.4
SDA14: J15.3, R30.1, U15.4
SDA15: J16.3, R32.1, U16.4
SDA16: J17.3, R34.1, U17.4
SDA17: J18.3, R36.1, U18.4
SDA18: J19.3, R38.1, U19.4
SDA19: J20.3, R40.1, U20.4
SDA20: J21.3, R42.1, U21.4
SDA21: J22.3, R44.1, U22.4
SDA22: J23.3, R46.1, U23.4
SDA23: J24.3, R48.1, U24.4
SDA24: J25.3, R50.1, U25.4
SDA25: J26.3, R52.1, U26.4
SDA26: J27.3, R54.1, U27.4
SDA27: J28.3, R56.1, U28.4
SDA28: J29.3, R58.1, U29.4
SDA29: J30.3, R60.1, U30.4
SDA30: J31.3, R62.1, U31.4
SDA31: J32.3, R64.1, U32.4
SDA32: J33.3, R66.1, U33.4
SDA33: J34.3, R68.1, U34.4
SDA34: J35.3, R70.1, U35.4
SDA35: J36.3, R72.1, U36.4
SDA36: J37.3, R74.1, U37.4
SDA37: J38.3, R76.1, U38.4
SDA38: J39.3, R78.1, U39.4
SDA39: J40.3, R80.1, U40.4
SDA40: J41.3, R82.1, U41.4
SDA41: J42.3, R84.1, U42.4
SDA42: J43.3, R86.1, U43.4
SDA43: J44.3, R88.1, U44.4
SDA44: J45.3, R90.1, U45.4
SDA45: J46.3, R92.1, U46.4
SDA46: J47.3, R94.1, U47.4
SDA47: J48.3, R96.1, U48.4
SDA48: J49.3, R98.1, U49.4
SDA49: J50.3, R100.1, U50.4
SDA50: J51.3, R102.1, U51.4
SDA51: J52.3, R104.1, U52.4
SDA52: J53.3, R106.1, U53.4
SDA53: J54.3, R108.1, U54.4
SDA54: J55.3, R110.1, U55.4
SDA55: J56.3, R112.1, U56.4
SDA56: J57.3, R114.1, U57.4
SDA57: J58.3, R116.1, U58.4
SDA58: J59.3, R118.1, U59.4
SDA59: J60.3, R120.1, U60.4
SDA60: J61.3, R122.1, U61.4
SDA61: J62.3, R124.1, U62.4
SDA62: J63.3, R126.1, U63.4
SDA63: J64.3, R128.1, U64.4
SDA64: J65.3, R130.1, U65.4
SDA65: J66.3, R132.1, U66.4
SDA66: J67.3, R134.1, U67.4
SDA67: J68.3, R136.1, U68.4
SDA68: J69.3, R138.1, U69.4
SDA69: J70.3, R140.1, U70.4
SDA70: J71.3, R142.1, U71.4
SDA71: J72.3, R144.1, U72.4
SDA72: J73.3, R146.1, U73.4
SDA73: J74.3, R148.1, U74.4
SDA74: J75.3, R150.1, U75.4
SDA75: J76.3, R152.1, U76.4
SDA76: J77.3, R154.1, U77.4
SDA77: J78.3, R156.1, U78.4
SDA78: J79.3, R158.1, U79.4
SDA79: J80.3, R160.1, U80.4
SDA80: J81.3, R162.1, U81.4
SDA81: J82.3, R164.1, U82.4
SDA82: J83.3, R166.1, U83.4
SDA83: J84.3, R168.1, U84.4
SDA84: J85.3, R170.1, U85.4
SDA85: J86.3, R172.1, U86.4
SDA86: J87.3, R174.1, U87.4
SDA87: J88.3, R176.1, U88.4
SDA88: J89.3, R178.1, U89.4
SDA89: J90.3, R180.1, U90.4
SDA90: J91.3, R182.1, U91.4
SDA91: J92.3, R184.1, U92.4
SDA92: J93.3, R186.1, U93.4
SDA93: J94.3, R188.1, U94.4
SDA94: J95.3, R190.1, U95.4
SDA95: J96.3, R192.1, U96.4
SDA96: J97.3, R194.1, U97.4
SDA97: J98.3, R196.1, U98.4
SDA98: J99.3, R198.1, U99.4
SDA99: J100.3, R200.1, U100.4
SDO_A/G: JP2.2, U1.5
SDO_A/G1: JP5.2, U2.5
SDO_A/G2: JP8.2, U3.5
SDO_A/G3: JP11.2, U4.5
SDO_A/G4: JP14.2, U5.5
SDO_A/G5: JP17.2, U6.5
SDO_A/G6: JP20.2, U7.5
SDO_A/G7: JP23.2, U8.5
SDO_A/G8: JP26.2, U9.5
SDO_A/G9: JP29.2, U10.5
SDO_A/G10: JP32.2, U11.5
SDO_A/G11: JP35.2, U12.5
SDO_A/G12: JP38.2, U13.5
SDO_A/G13: JP41.2, U14.5
SDO_A/G14: JP44.2, U15.5
SDO_A/G15: JP47.2, U16.5
SDO_A/G16: JP50.2, U17.5
SDO_A/G17: JP53.2, U18.5
SDO_A/G18: JP56.2, U19.5
SDO_A/G19: JP59.2, U20.5
SDO_A/G20: JP62.2, U21.5
SDO_A/G21: JP65.2, U22.5
SDO_A/G22: JP68.2, U23.5
SDO_A/G23: JP71.2, U24.5
SDO_A/G24: JP74.2, U25.5
SDO_A/G25: JP77.2, U26.5
SDO_A/G26: JP80.2, U27.5
SDO_A/G27: JP83.2, U28.5
SDO_A/G28: JP86.2, U29.5
SDO_A/G29: JP89.2, U30.5
SDO_A/G30: JP92.2, U31.5
SDO_A/G31: JP95.2, U32.5
SDO_A/G32: JP98.2, U33.5
SDO_A/G33: JP101.2, U34.5
SDO_A/G34: JP104.2, U35.5
SDO_A/G35: JP107.2, U36.5
SDO_A/G36: JP110.2, U37.5
SDO_A/G37: JP113.2, U38.5
SDO_A/G38: JP116.2, U39.5
SDO_A/G39: JP119.2, U40.5
SDO_A/G40: JP122.2, U41.5
SDO_A/G41: JP125.2, U42.5
SDO_A/G42: JP128.2, U43.5
SDO_A/G43: JP131.2, U44.5
SDO_A/G44: JP134.2, U45.5
SDO_A/G45: JP137.2, U46.5
SDO_A/G46: JP140.2, U47.5
SDO_A/G47: JP143.2, U48.5
SDO_A/G48: JP146.2, U49.5
SDO_A/G49: JP149.2, U50.5
SDO_A/G50: JP152.2, U51.5
SDO_A/G51: JP155.2, U52.5
SDO_A/G52: JP158.2, U53.5
SDO_A/G53: JP161.2, U54.5
SDO_A/G54: JP164.2, U55.5
SDO_A/G55: JP167.2, U56.5
SDO_A/G56: JP170.2, U57.5
SDO_A/G57: JP173.2, U58.5
SDO_A/G58: JP176.2, U59.5
SDO_A/G59: JP179.2, U60.5
SDO_A/G60: JP182.2, U61.5
SDO_A/G61: JP185.2, U62.5
SDO_A/G62: JP188.2, U63.5
SDO_A/G63: JP191.2, U64.5
SDO_A/G64: JP194.2, U65.5
SDO_A/G65: JP197.2, U66.5
SDO_A/G66: JP200.2, U67.5
SDO_A/G67: JP203.2, U68.5
SDO_A/G68: JP206.2, U69.5
SDO_A/G69: JP209.2, U70.5
SDO_A/G70: JP212.2, U71.5
SDO_A/G71: JP215.2, U72.5
SDO_A/G72: JP218.2, U73.5
SDO_A/G73: JP221.2, U74.5
SDO_A/G74: JP224.2, U75.5
SDO_A/G75: JP227.2, U76.5
SDO_A/G76: JP230.2, U77.5
SDO_A/G77: JP233.2, U78.5
SDO_A/G78: JP236.2, U79.5
SDO_A/G79: JP239.2, U80.5
SDO_A/G80: JP242.2, U81.5
SDO_A/G81: JP245.2, U82.5
SDO_A/G82: JP248.2, U83.5
SDO_A/G83: JP251.2, U84.5
SDO_A/G84: JP254.2, U85.5
SDO_A/G85: JP257.2, U86.5
SDO_A/G86: JP260.2, U87.5
SDO_A/G87: JP263.2, U88.5
SDO_A/G88: JP266.2, U89.5
SDO_A/G89: JP269.2, U90.5
SDO_A/G90: JP272.2, U91.5
SDO_A/G91: JP275.2, U92.5
SDO_A/G92: JP278.2, U93.5
SDO_A/G93: JP281.2, U94.5
SDO_A/G94: JP284.2, U95.5
SDO_A/G95: JP287.2, U96.5
SDO_A/G96: JP290.2, U97.5
SDO_A/G97: JP293.2, U98.5
SDO_A/G98: JP296.2, U99.5
SDO_A/G99: JP299.2, U100.5
SDO_M: JP3.2, U1.6
SDO_M1: JP6.2, U2.6
SDO_M2: JP9.2, U3.6
SDO_M3: JP12.2, U4.6
SDO_M4: JP15.2, U5.6
SDO_M5: JP18.2, U6.6
SDO_M6: JP21.2, U7.6
SDO_M7: JP24.2, U8.6
SDO_M8: JP27.2, U9.6
SDO_M9: JP30.2, U10.6
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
